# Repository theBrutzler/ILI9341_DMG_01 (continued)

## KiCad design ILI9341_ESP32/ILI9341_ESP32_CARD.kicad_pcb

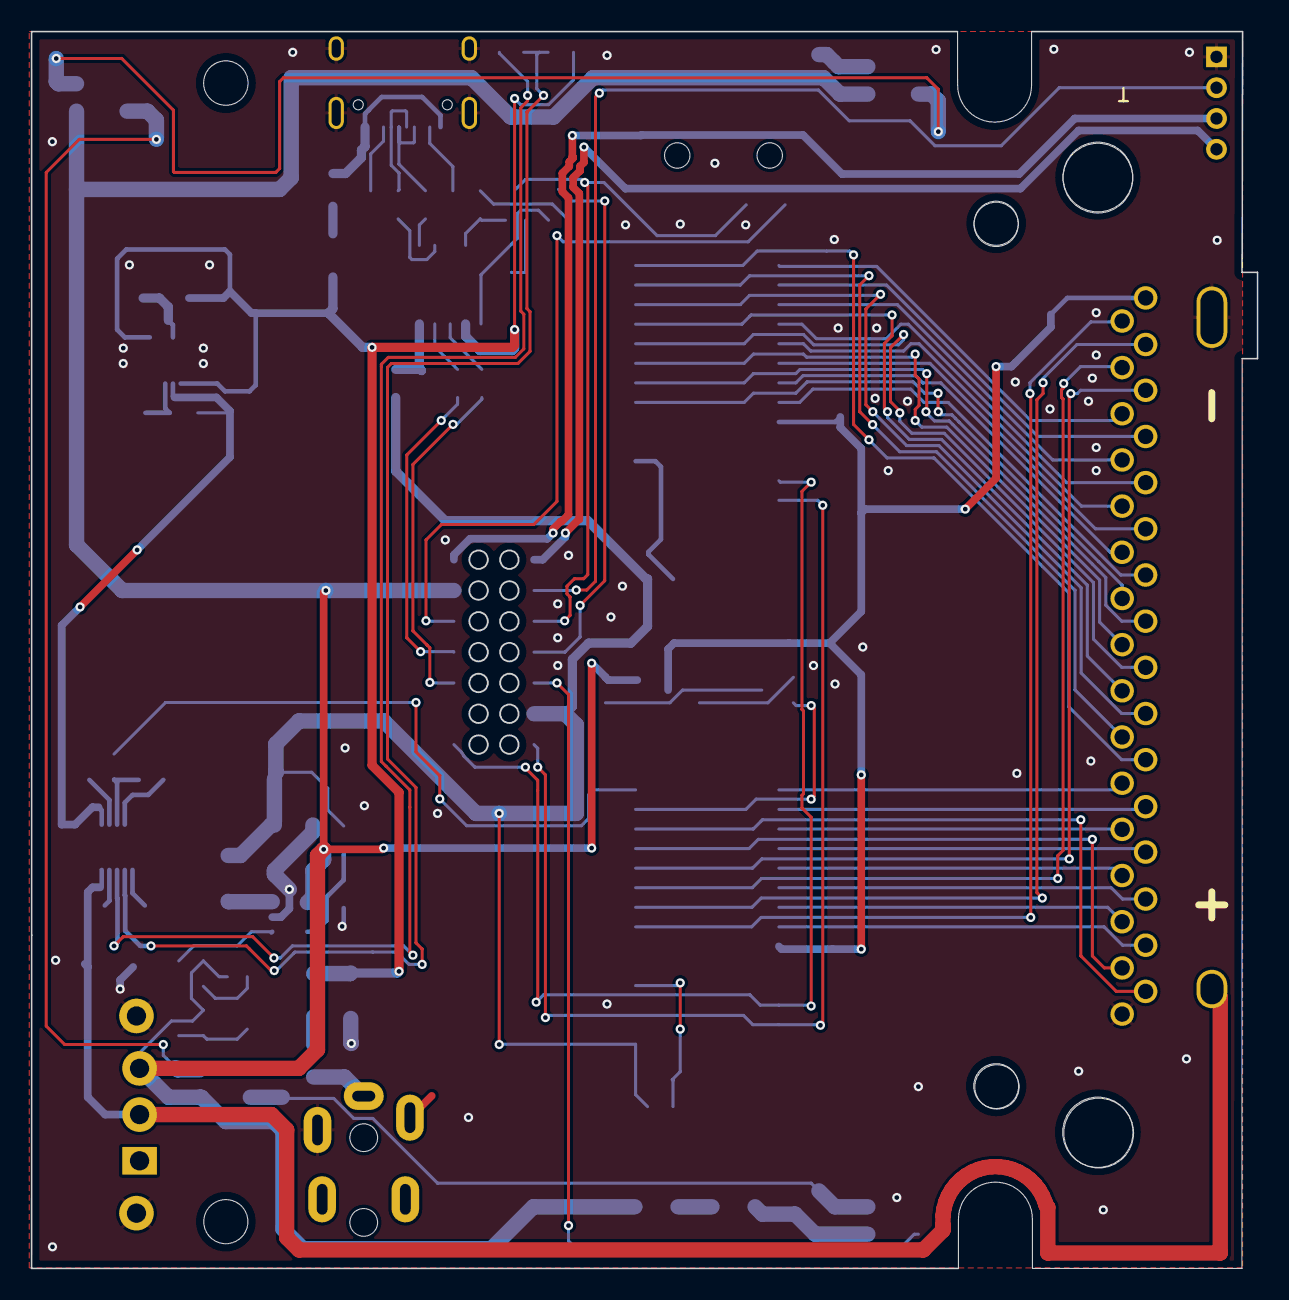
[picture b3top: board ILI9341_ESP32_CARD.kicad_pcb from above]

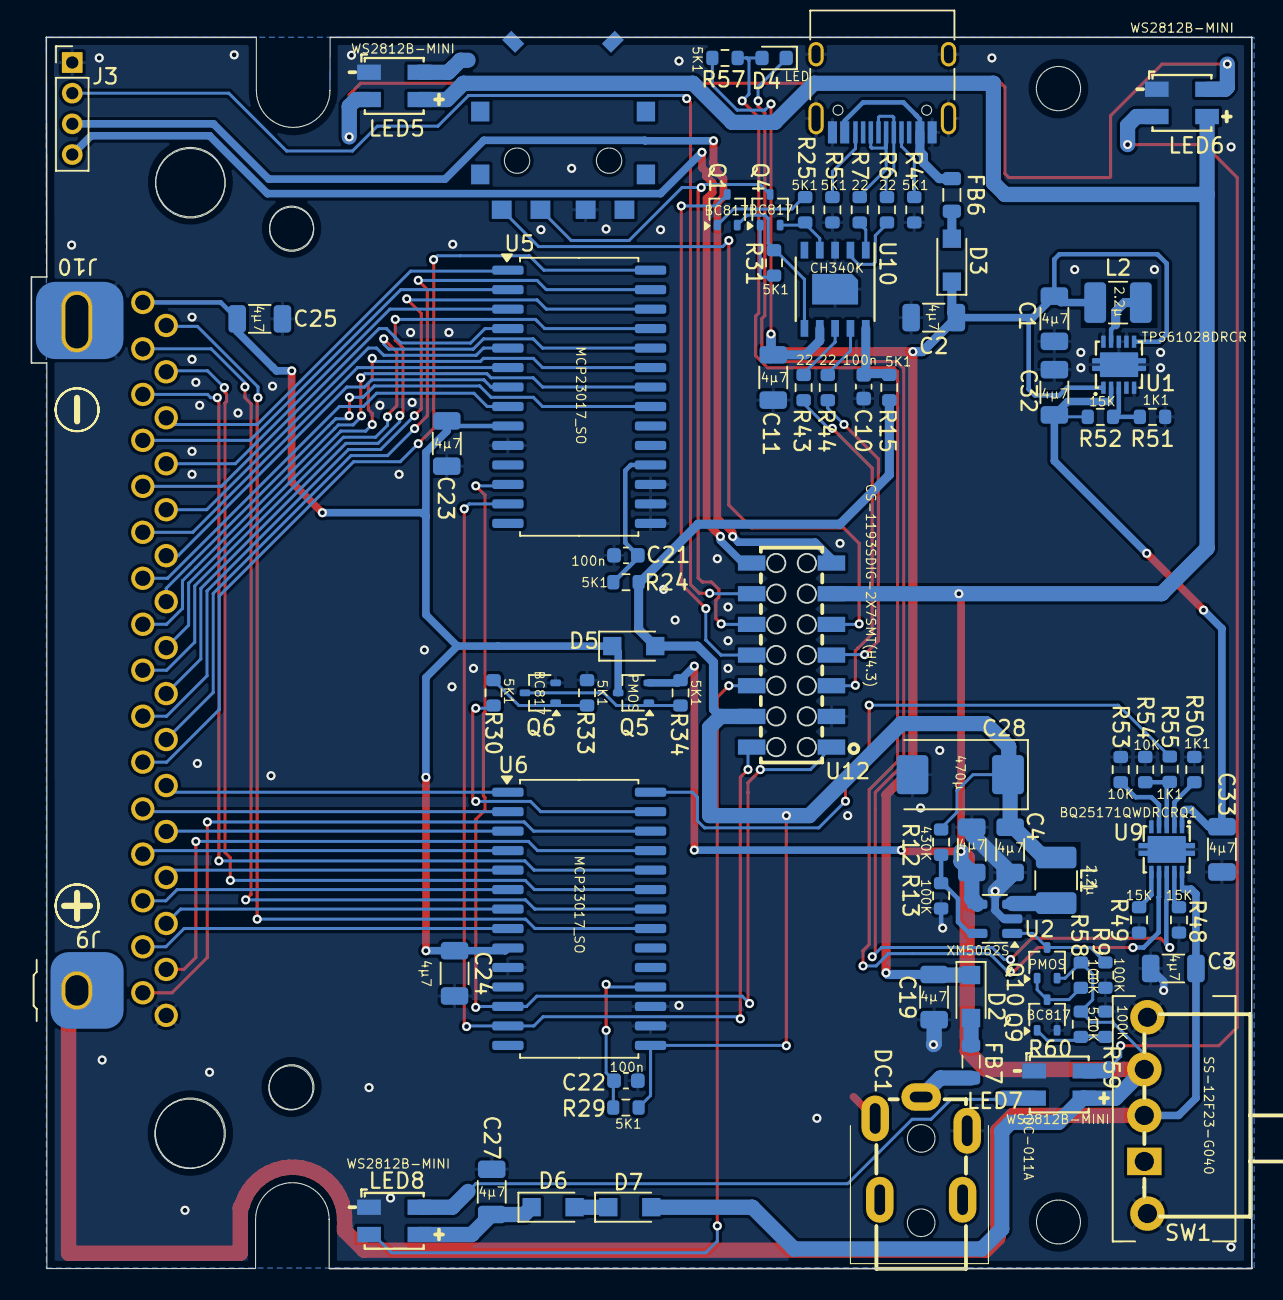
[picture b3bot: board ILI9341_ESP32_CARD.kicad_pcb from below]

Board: 2 copper layers, 79.6 x 80.3 mm, 83 parts (83 on the bottom side), 90 nets.

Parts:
BT1: Battery_Cell; BATTERY_AA_SMD_PLUS
BT2: Battery_Cell; BATTERY_AA_SMD_MINUS
C1, C2, C3, C4, C8, C11, C19, C23, C24, C25, C27, C32, C33: 4µ7; C_1206_3216Metric
C10, C21, C22: 100n; C_0603_1608Metric
C28: 470µ; CP_EIA-7343-43_Kemet-X
D2, D3, D5, D6, D7: D; Nexperia_CFP3_SOD-123W
D4: LED; LED_0603_1608Metric
DC1: DC-011A; DC-IN-TH_DC-011A
FB6, FB7: FerriteBead_Small; L_0805_2012Metric
J1: USB_C_Receptacle_USB2.0_16P; USB_C_Receptacle_HRO_TYPE-C-31-M-12
J3: Conn_01x04_Socket; PinHeader_1x04_P2.00mm_Vertical
J7: Conn_01x32; DMG_01_CARDRIDGE_CONNECTOR
J9: Conn_01x01_Pin; NINTENDO_PLUS
J10: Conn_01x01_Pin; NINTENDO_MINUS
L1, L2: 2.2µ; L_1210_3225Metric_Pad1.42x2.65mm_HandSolder
LED5, LED6, LED7, LED8: WS2812B-MINI; LED-SMD_4P-L3.5-W3.5-TL_WS2812B
Q1, Q4, Q6, Q9: BC817; SOT-323_SC-70
Q5, Q10: PMOS; SOT-323_SC-70
R4, R5, R15, R24, R25, R29, R30, R31, R33, R34, R57: 5K1; R_0603_1608Metric
R6, R7, R43, R44: 22; R_0603_1608Metric
R9, R13, R58, R59: 100K; R_0603_1608Metric
R12: 430K; R_0603_1608Metric
R48, R49, R52: 15K; R_0603_1608Metric
R50, R51, R55: 1K1; R_0603_1608Metric
R53, R54: 10K; R_0603_1608Metric
R60: 510K; R_0603_1608Metric
SW1: SS-12F23-G040; SW-TH_SS-12F23-G040
U1: TPS61028DRCR; VSON-10_L3.0-W3.0-P0.50-TL-EP-1
U2: XM5062S; SOT-23-5
U5, U6: MCP23017_SO; SOIC-28W_7.5x17.9mm_P1.27mm
U7: 02FVS3
U9: BQ25171QWDRCRQ1; VSON-10_L3.0-W3.0-P0.50-BL-EP1.65
U10: CH340K; SSOP-10_3.9x4.9mm_P1.00mm_EP_3mmx2mm
U12: CS-1193SDIG-2X7SMT(H4.3); PM200-2-07-S-4.3

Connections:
+3V3: C4.1, C28.1, D5.2 (A), L1.2, R12.1, R15.2, R24.1, R29.1, U6.15 (A0), U12.4
/AUDIO/AUDIO_DETECT: J3.2, U12.12
/AUDIO/AUDIO_LEFT: J3.3, U12.13
/AUDIO/AUDIO_RIGHT: J3.4, U12.14
/CHARGER_EN: R55.2, U6.28 (GPA7)
/D+: R7.2, U10.1 (UD+)
/D-: R6.1, U10.2 (UD-)
/DMG_CARD/CARD_A0: J7.6, U5.1 (GPB0)
/DMG_CARD/CARD_A1: J7.7, U5.2 (GPB1)
/DMG_CARD/CARD_A2: J7.8, U5.3 (GPB2)
/DMG_CARD/CARD_A3: J7.9, U5.4 (GPB3)
/DMG_CARD/CARD_A4: J7.10, U5.5 (GPB4)
/DMG_CARD/CARD_A5: J7.11, U5.6 (GPB5)
/DMG_CARD/CARD_A6: J7.12, U5.7 (GPB6)
/DMG_CARD/CARD_A7: J7.13, U5.8 (GPB7)
/DMG_CARD/CARD_A8: J7.14, U5.21 (GPA0)
/DMG_CARD/CARD_A9: J7.15, U5.22 (GPA1)
/DMG_CARD/CARD_A10: J7.16, U5.23 (GPA2)
/DMG_CARD/CARD_A11: J7.17, U5.24 (GPA3)
/DMG_CARD/CARD_A12: J7.18, U5.25 (GPA4)
/DMG_CARD/CARD_A13: J7.19, U5.26 (GPA5)
/DMG_CARD/CARD_A14: J7.20, U5.27 (GPA6)
/DMG_CARD/CARD_A15: J7.21, U5.28 (GPA7)
/DMG_CARD/CARD_CLK: J7.2, U6.21 (GPA0)
/DMG_CARD/CARD_D0: J7.22, U6.1 (GPB0)
/DMG_CARD/CARD_D1: J7.23, U6.2 (GPB1)
/DMG_CARD/CARD_D2: J7.24, U6.3 (GPB2)
/DMG_CARD/CARD_D3: J7.25, U6.4 (GPB3)
/DMG_CARD/CARD_D4: J7.26, U6.5 (GPB4)
/DMG_CARD/CARD_D5: J7.27, U6.6 (GPB5)
/DMG_CARD/CARD_D6: J7.28, U6.7 (GPB6)
/DMG_CARD/CARD_D7: J7.29, U6.8 (GPB7)
/DMG_CARD/CARD_SCL: U5.12 (SCK), U6.12 (SCK), U12.1
/DMG_CARD/CARD_SDA: U5.13 (SDA), U6.13 (SDA), U12.2
/DMG_CARD/CARD_VCC: C23.1, C24.1, C25.1, D5.1 (K), J7.1, Q5.3 (D), U5.9 (VDD), U6.9 (VDD)
/DMG_CARD/CARD_VIN: J7.31, U6.26 (GPA5)
/DMG_CARD/CARD_VOLTAGE: Q5.1 (G), Q6.3 (C), R34.2
/DMG_CARD/CARD_~CS: J7.5, U6.24 (GPA3)
/DMG_CARD/CARD_~RD: J7.4, U6.23 (GPA2)
/DMG_CARD/CARD_~RES: J7.30, U6.25 (GPA4)
/DMG_CARD/CARD_~WR: J7.3, U6.22 (GPA1)
/DTR: Q4.2 (E), R25.1, U10.4 (~DTR)
/EN: Q1.3 (C), U12.8
/FRONT_BUTTONS/xLED: LED8.4 (DIN), U12.6
/KEY_MENU: U7.A, U12.9
/KEY_OPTION: Q4.3 (C), U7.S, U12.10
/RTS: Q1.2 (E), R31.1, U10.6 (~RTS)
/RXD: R43.1, U12.5
/STAT1: D4.2 (A), R57.2, U9.7 (STAT1)
/STAT2: D4.1 (K), U9.8 (STAT2)
/TXD: R44.1, U12.7
/VUSB: C1.1, C2.1, C11.1, C19.1, D2.1 (K), D3.1 (K), L2.1, R57.1, U1.1 (EN), U1.6 (VBAT), U10.7 (VCC)
/V_BATT: C8.1, D7.2 (A), LED5.1 (VDD), LED6.1 (VDD), LED7.1 (VDD), Q5.2 (S), Q10.2 (S), R34.1, R58.1, R60.1, SW1.3, U2.4 (VIN), U12.11
GND: BT2.2 (-), C1.2, C2.2, C3.2, C4.2, C8.2, C10.2, C11.2, C19.2, C21.1, C22.1, C23.2, C24.2, C25.2, C27.2, C28.2, C32.1, C33.1, DC1.3, J1.A1 (GND), J1.A12 (GND), J1.B1 (GND), J1.B12 (GND), J1.S1 (SHIELD), J3.1, J7.32, J10.1, LED5.3 (VSS), LED6.3 (VSS), LED7.3 (VSS), LED8.3 (VSS), Q6.2 (E), Q9.2 (E), R4.1, R5.2, R9.2, R13.2, R33.2, R48.1, R49.1, R50.2, R51.1, R53.2, R54.1, R59.2, SW1.4, SW1.5, U1.5 (GND), U1.7 (LBI), U1.8 (PS), U1.10 (PGND), U1.11 (EP), U2.2 (GND), U5.10 (VSS), U5.15 (A0), U5.16 (A1), U5.17 (A2), U6.10 (VSS), U6.16 (A1), U6.17 (A2), U7.C, U9.5 (GND), U9.11 (EP), U10.3 (GND), U10.PAD (GND), U12.3
unnamed: BT1.1 (+), C3.1, J9.1, SW1.2, U9.10 (OUT)
unnamed: D2.2 (A), FB7.2
unnamed: D3.2 (A), FB6.2
unnamed: D6.2 (A), D7.1 (K)
unnamed: C27.1, D6.1 (K), LED8.1 (VDD)
unnamed: DC1.2, FB7.1
unnamed: FB6.1, J1.A4 (VBUS), J1.A9 (VBUS), J1.B4 (VBUS), J1.B9 (VBUS)
unnamed: J1.A5 (CC1), R4.2
unnamed: J1.B5 (CC2), R5.1
unnamed: J1.A6 (D+), J1.B6 (D+), R7.1
unnamed: J1.A7 (D-), J1.B7 (D-), R6.2
unnamed: LED5.4 (DIN), LED6.2 (DOUT)
unnamed: LED6.4 (DIN), LED7.2 (DOUT)
unnamed: LED7.4 (DIN), LED8.2 (DOUT)
unnamed: Q1.1 (B), R25.2
unnamed: Q4.1 (B), R31.2
unnamed: Q6.1 (B), R30.2, R33.1
unnamed: Q9.1 (B), R59.1, R60.2
unnamed: Q10.3 (D), R9.1, U2.1 (EN)
unnamed: Q9.3 (C), Q10.1 (G), R58.2
unnamed: R51.2, R52.1, U1.3 (FB)
unnamed: L2.2, U1.9 (SW)
unnamed: C32.2, C33.2, R52.2, U1.2 (VOUT), U9.1 (IN)
unnamed: R12.2, R13.1, U2.5 (FB)
unnamed: L1.1, U2.3 (SW)
unnamed: C21.2, R24.2, U5.18 (~RESET)
unnamed: R30.1, U6.27 (GPA6)
unnamed: C22.2, R29.2, U6.18 (~RESET)
unnamed: R49.2, U9.6 (CHM_TMR)
unnamed: R50.1, U9.2 (ISET)
unnamed: R53.1, U9.4 (TS)
unnamed: R48.2, U9.9 (VSET)
unnamed: R54.2, R55.1, U9.3 (~CE)
unnamed: R44.2, U10.9 (RXD)
unnamed: R43.2, U10.8 (TXD)
unnamed: C10.1, R15.1, U10.10 (V3)

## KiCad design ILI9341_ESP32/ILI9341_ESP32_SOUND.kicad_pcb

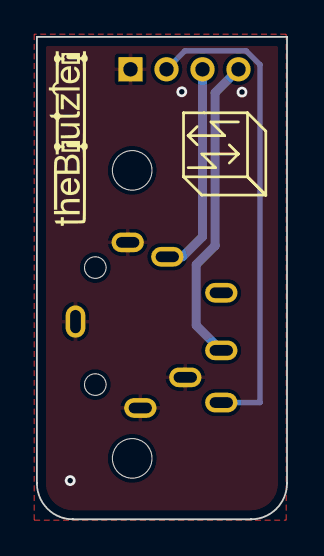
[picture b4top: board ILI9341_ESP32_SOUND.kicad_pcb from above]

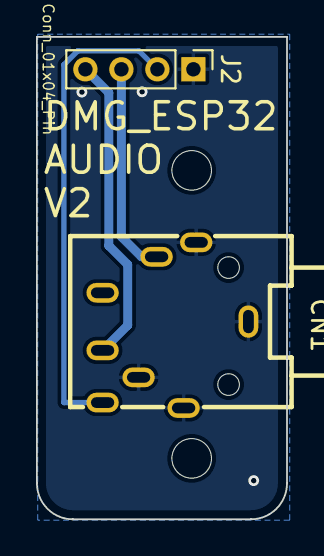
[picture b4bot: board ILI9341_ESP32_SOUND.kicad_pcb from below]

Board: 2 copper layers, 13.9 x 26.8 mm, 5 parts (4 on the bottom side), 4 nets.

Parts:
CN1: PJ-3043-B; AUDIO-TH_PJ-3043-B
H1, H2: MountingHole; MountingHole_2.2mm_M2
J2: Conn_01x04_Pin; PinHeader_1x04_P2.00mm_Vertical
SM3: SYM_Arrow45_Tiny; Symbol_kurzschlussblog

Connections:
unnamed: CN1.1, CN1.5, CN1.8, J2.1
unnamed: CN1.6, J2.2
unnamed: CN1.3, J2.3
unnamed: CN1.2, J2.4

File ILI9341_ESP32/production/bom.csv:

Designator,Footprint,Quantity,Value,LCSC Part #
CN1,AUDIO-TH_PJ-3043-B,1,PJ-3043-B,
SM3,Symbol_kurzschlussblog,1,SYM_Arrow45_Tiny,

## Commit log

2024-05-13 Initial Upload
    Not finished yet
2024-05-16 Add new connection (inter PCB)
    build up new concept to fit in original gameboy case :) hope so
    sound tested on prototyp wirering
2024-05-19 Update ESP from S3 to WROVER
    Changed ESP to be compatible to odroid-go
2024-05-28 update cardridge grabber funktion
2024-06-01 update routing and put display on front pcb
2024-06-01 add schematic pdf
2024-06-18 update to funktion version without 5khz noise on audio amp
2024-06-18 zwischenstand v2
2024-06-20 Update PCB and add RGB
2024-06-25 zwischenstand battery pcb finished
2024-06-27 update nimh charger and battery protection
2024-06-27 remove interpcb connection (not mousebites mousebites)
2024-07-02 ordered Version
2024-07-30 upload new untested version
    the boosconverter should work now :)
